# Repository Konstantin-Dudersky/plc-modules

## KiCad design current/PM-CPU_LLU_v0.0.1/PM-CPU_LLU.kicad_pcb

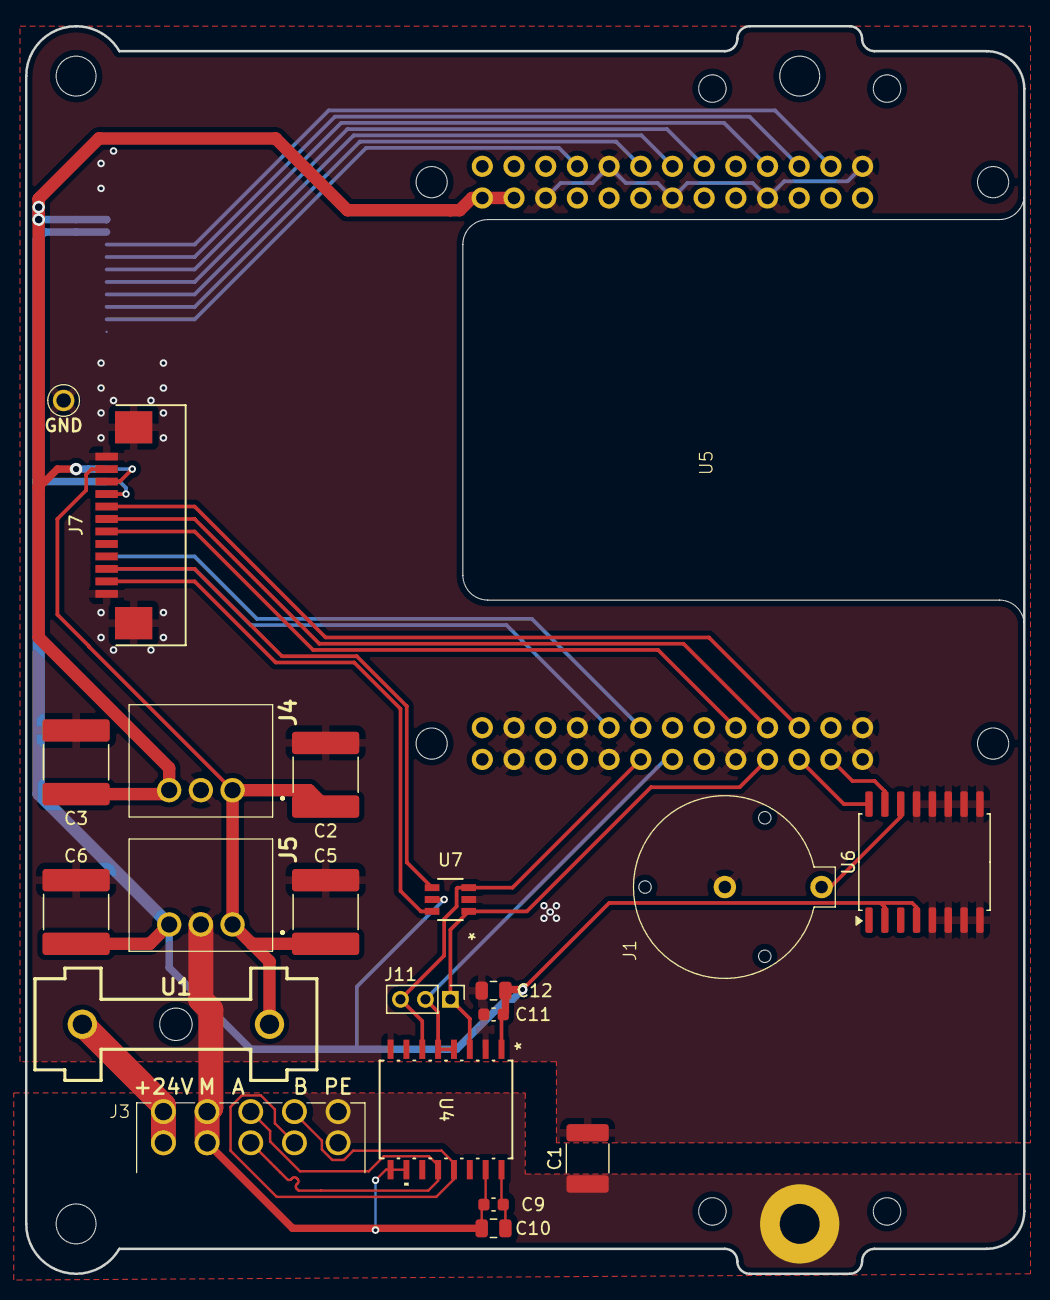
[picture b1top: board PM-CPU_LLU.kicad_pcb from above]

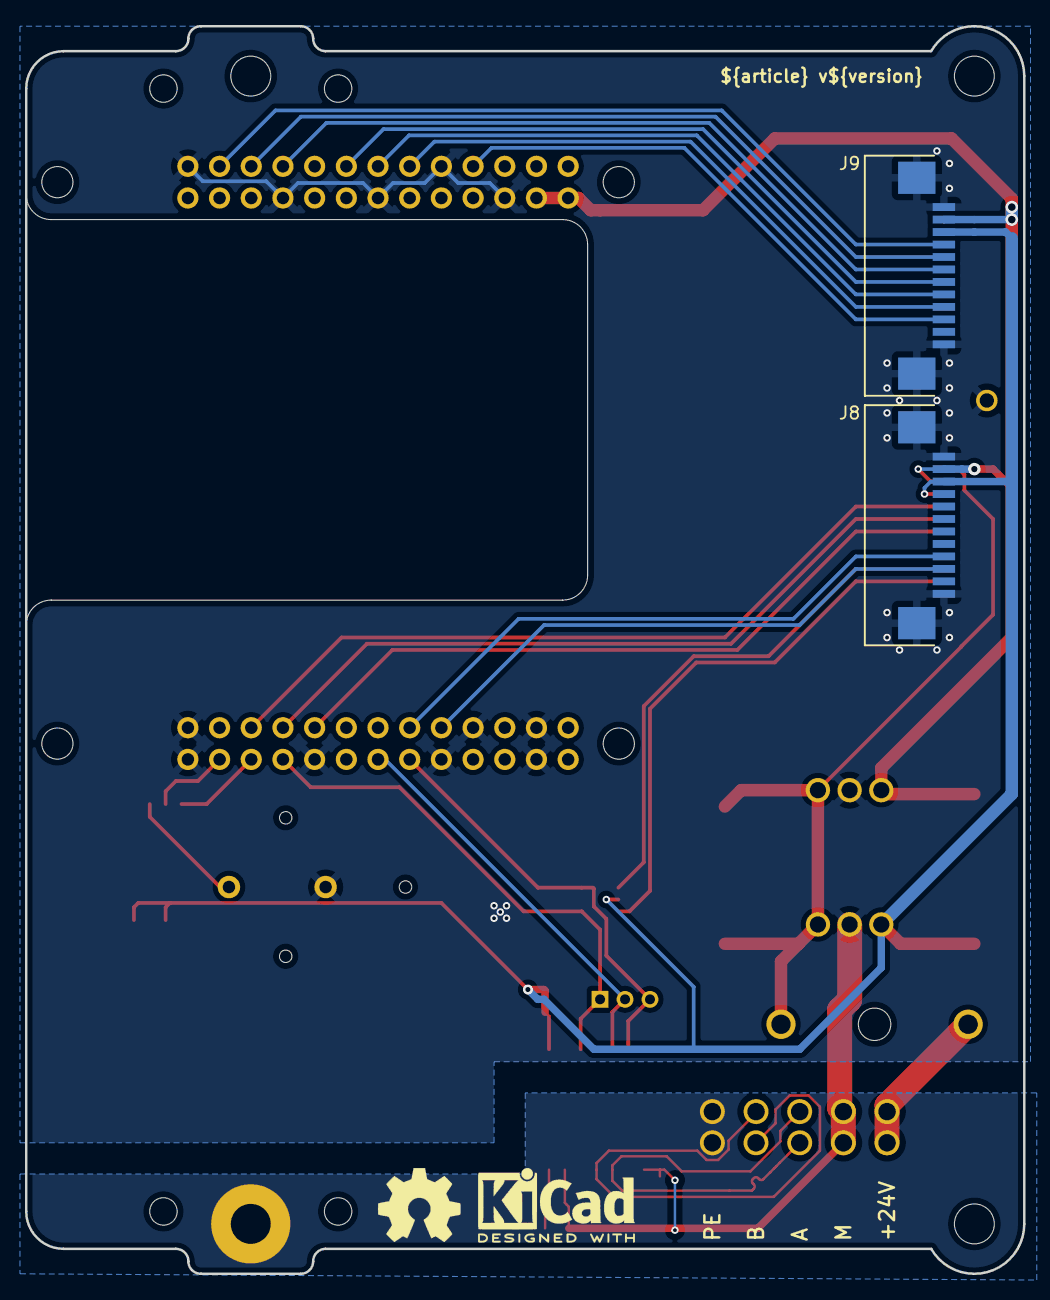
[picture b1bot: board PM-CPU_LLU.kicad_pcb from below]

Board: 2 copper layers, 80.0 x 100.0 mm, 30 parts (4 on the bottom side), 29 nets.

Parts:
C1: 4.7nF 2kV; C_1812_4532Metric
C2, C3, C5, C6: 22uF; C_2220_5750Metric
C9, C11: 100nF; C_0603_1608Metric
C10, C12: 10uF; C_0805_2012Metric
H1, H2, H3: MountingHole_M3
J1: BS-12-A1AJ002-F
J3: 15EDGRHC-THR-3.5-10P
J4: K7805-2000R3
J5: K7803-2000R3; K7805-2000R3
J7, J8, J9: AFA07-S10FCC-00; CONN10_AFA07-S12_JUS
J11: PinHeader_01x03_P2.00_THT_straight; PinHeader_1x03_P2.00mm_Vertical
PE1: PE
SP1: PM_LED-xx-v0.0.1
U1: 64900001039; 649-Series-Holder
U2: 5117
U4: CA-IS3098W; SOIC16-WBW_CLG
U5: LuckfoxLyraUltra
U6: DS3231; SOIC-16W_7.5x10.3mm_P1.27mm
U7: SN74LVC2G14DBVR; DBV6-M
kicad_logo: KiCad-Logo2_5mm_SilkScreen
oshw_logo: OSHW-Symbol_6.7x6mm_SilkScreen

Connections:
+3.3V_BUS: C9.1, C10.1, U4.16 (VISO)
+3.3V_CPU: C6.1, C11.1, C12.1, J5.3 (+VO), J7.9, J8.3, J9.3, U4.1 (VDD), U6.2 (VCC), U6.4 (~RST), U7.5 (VCC)
+5V_CPU: C3.1, J4.3 (+VO), J7.10, J8.2, J9.2, U5.10 (VSYS), U5.11 (VSYS)
+24V_BUS: J3.1, J3.6 (Pin_2), U1.1
+24V_fuse: C2.1, C5.1, J4.1 (VIN), J5.1 (VIN), J7.11, U1.2
/A: J3.3, J3.8 (Pin_6), U4.12 (A)
/B: J3.4, J3.9 (Pin_8), U4.13 (B)
/I2C0_SCL: J8.10, U5.24 (RM_IO24)
/I2C0_SDA: J8.9, U5.25 (RM_IO25)
/I2C1_SCL: U5.3A (RM_IO18), U6.16 (SCL)
/I2C1_SDA: U5.3B (RM_IO20), U6.15 (SDA)
/LED_0: J7.8, U5.2A (RM_IO30)
/LED_1: J7.7, U5.29 (RM_IO29)
/LED_2: J7.6, U5.28 (RM_IO28)
/SPI_CS0: J9.7, U5.07 (RM_IO5)
/SPI_CS1: J9.8, U5.06 (RM_IO4)
/SPI_CS2: J9.9, U5.05 (RM_IO3)
/SPI_CS3: J9.10, U5.03 (RM_IO2)
/SPI_MISO: J9.5, U5.0A (RM_IO7)
/SPI_MOSI: J9.4, U5.0B (RM_IO8)
/SPI_SCK: J9.6, U5.09 (RM_IO6)
/UART_RTS: J11.2, U4.4 (RE), U4.5 (DE), U5.36
/UART_RX: J11.1, U4.3 (RO), U5.39 (RM_IO17), U7.1 (1A)
/UART_RX_LED: J7.2, U7.6 (1Y)
/UART_TX: J11.3, U4.6 (DI), U5.35 (RM_IO16), U7.3 (2A)
/UART_TX_LED: J7.3, U7.4 (2Y)
/Vbat: J1.1, U6.14 (VBAT)
GND_BUS: C1.2, C2.2, C3.2, C5.2, C6.2, C9.2, C10.2, C11.2, C12.2, J1.2, J3.2 (Pin_3), J3.7 (Pin_4), J4.2 (GND), J5.2 (GND), J7.1, J7.12 (Pin_11), J7.13 (Pin_11), J8.1, J8.12 (Pin_11), J8.13 (Pin_11), J9.1, J9.12 (Pin_11), J9.13 (Pin_11), U2.1, U4.2 (GNDA), U4.8 (GNDA), U4.9 (GNDB), U4.10 (SEL), U4.15 (GNDB), U5.0C (GND), U5.2C (GND), U5.3C (GND), U5.04 (GND), U5.12 (GND), U5.16 (GND), U5.19 (GND), U5.21 (GND), U5.23 (GND), U5.31 (GND), U5.34 (GND), U5.38 (GND), U6.5 (GND), U6.6 (GND), U6.7 (GND), U6.8 (GND), U6.9 (GND), U6.10 (GND), U6.11 (GND), U6.12 (GND), U6.13 (GND), U7.2 (GND)
PE: C1.1, J3.5 (Pin_9), J3.10, PE1.1

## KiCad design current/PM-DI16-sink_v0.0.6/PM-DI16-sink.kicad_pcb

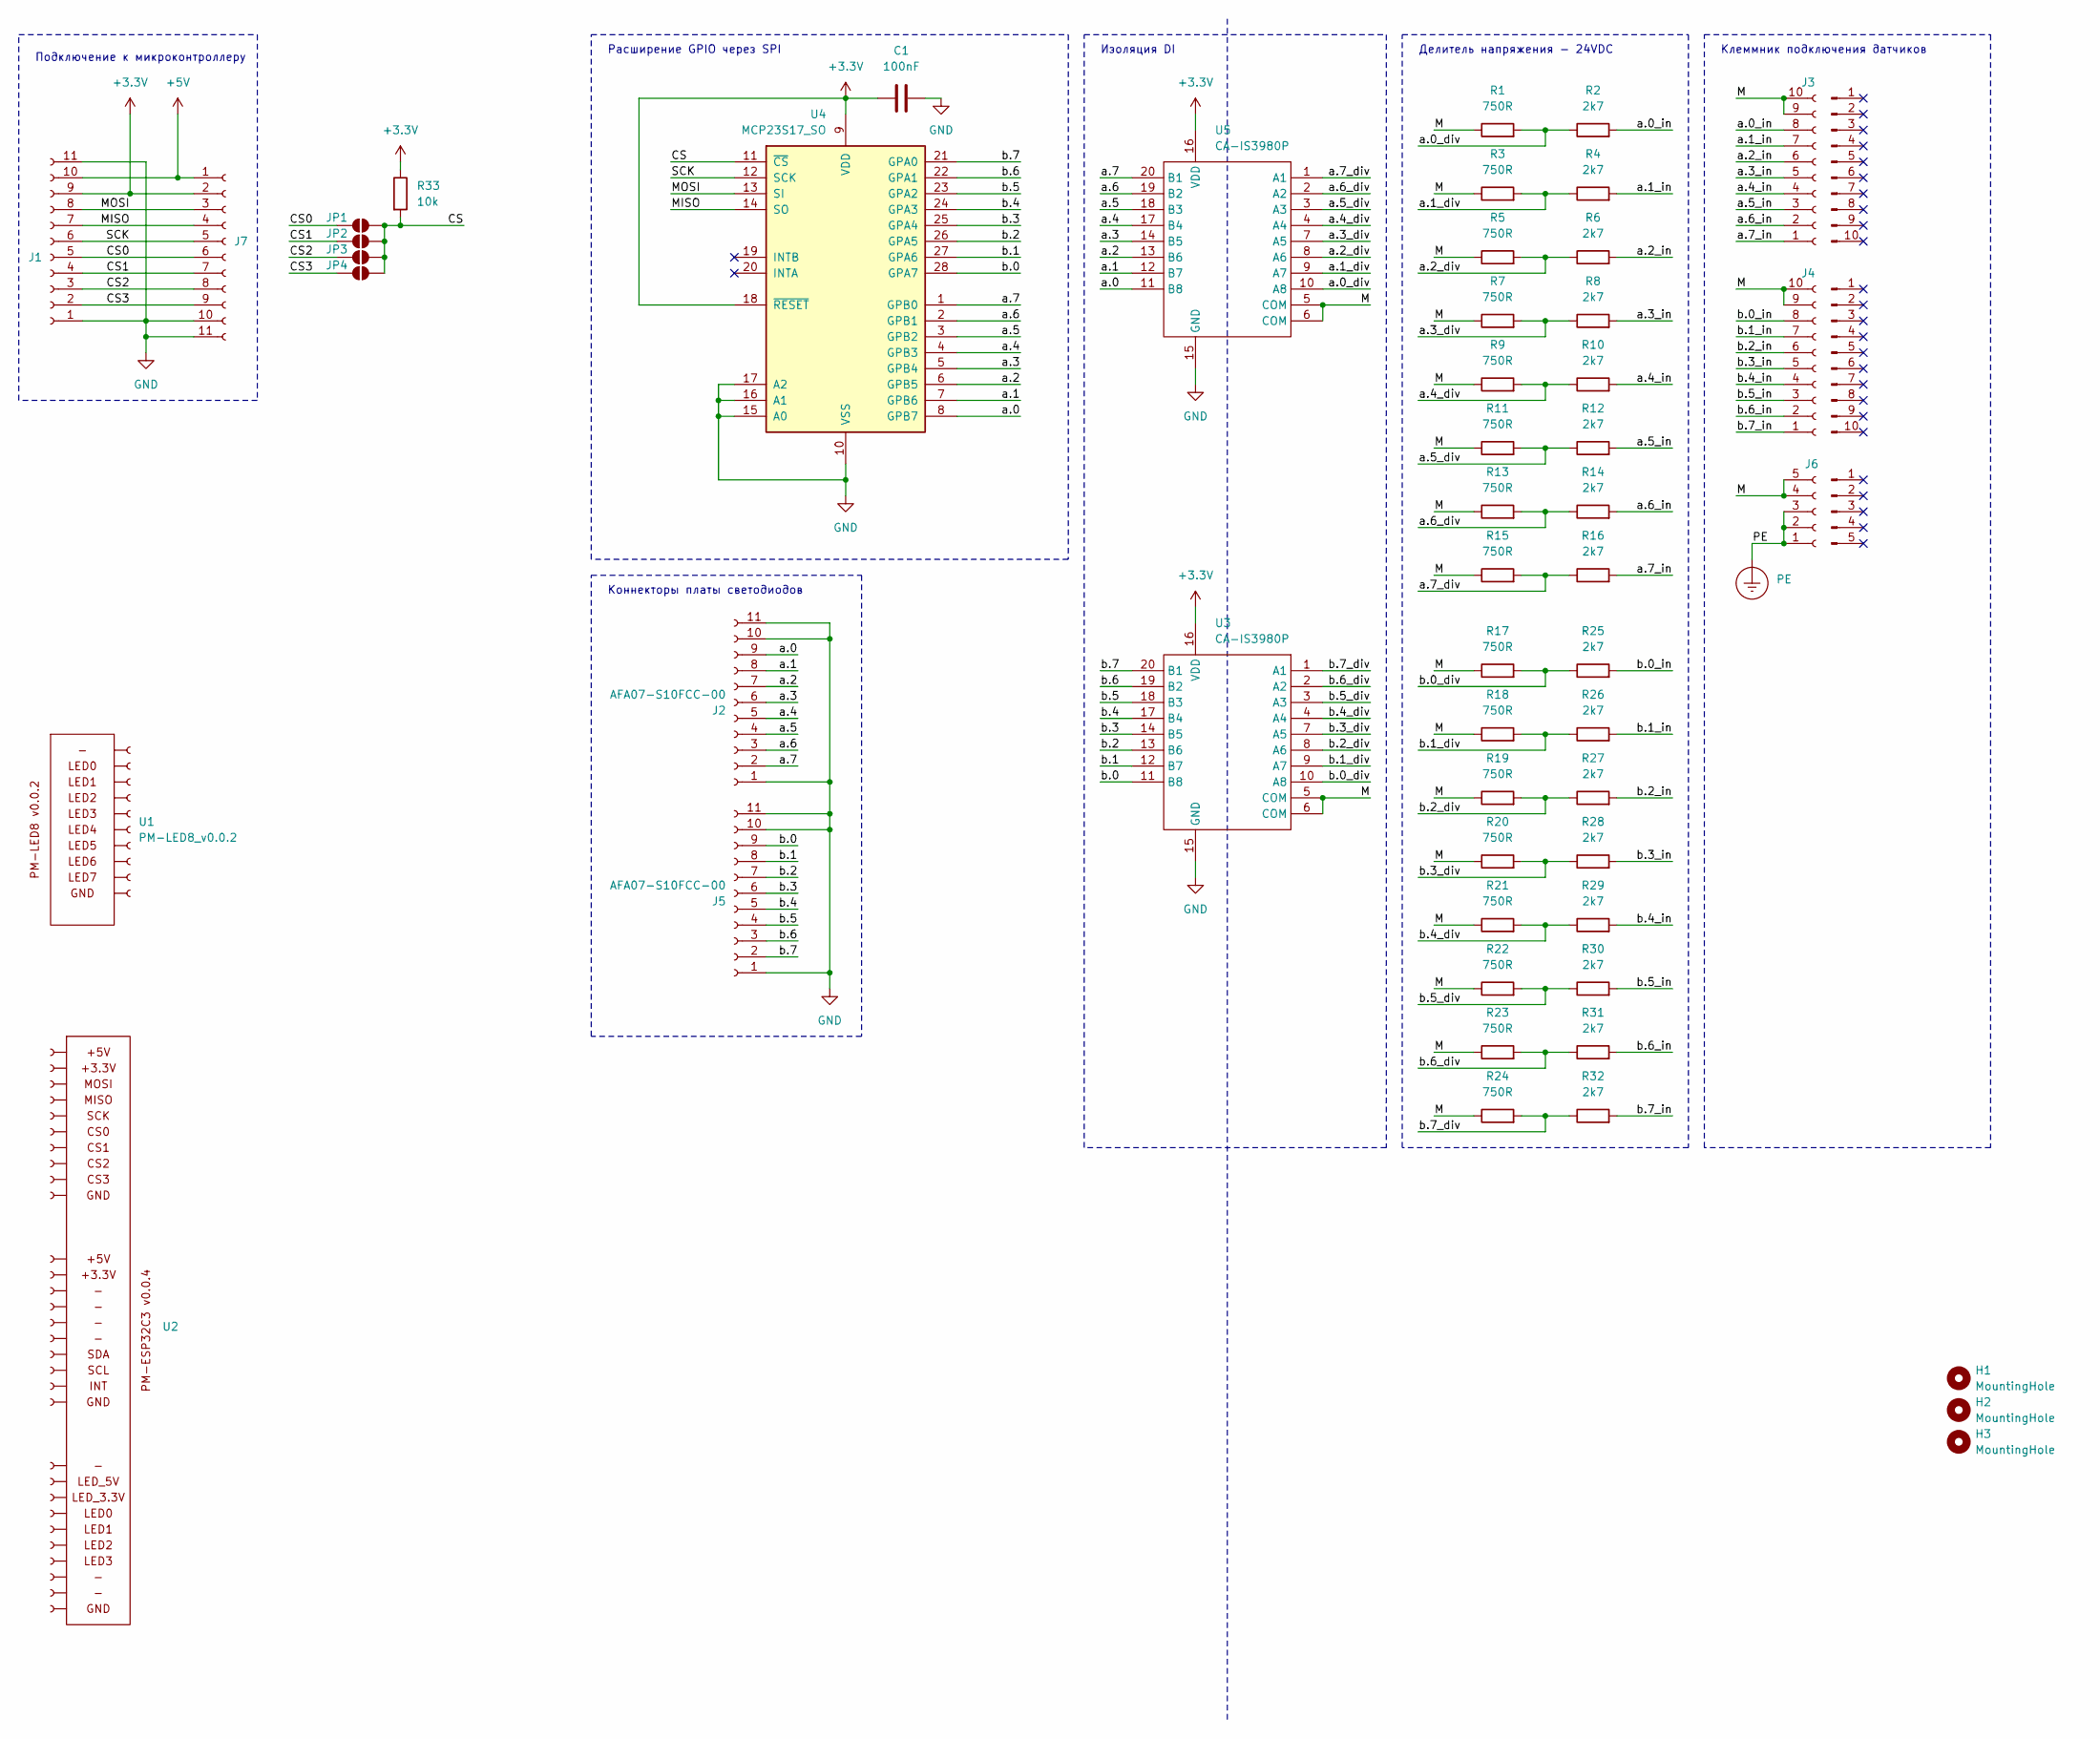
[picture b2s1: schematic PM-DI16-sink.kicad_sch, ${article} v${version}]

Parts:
C1: 100nF; C_0603_1608Metric; part_ipn C_100nF_16V_0603_MLCC-X7R
H1, H2, H3: MountingHole; MountingHole_3.2mm_M3
J1, J2, J5, J7: AFA07-S10FCC-00; CONN10_AFA07-S10_JUS; part_ipn AFA07-S10FCC-00
J3, J4: 15EDGRC-3.5-10P; part_ipn 15EDGRC-3.5-10P
J6: 15EDGRC-3.5-05P; part_ipn 15EDGRC-3.5-05P
J8, J9: 15EDGK-3.5-10P; part_ipn 15EDGK-3.5-10P
J10: 15EDGK-3.5-05P; part_ipn 15EDGK-3.5-05P
JP1, JP2, JP3, JP4: SolderJumper_2_Open; SolderJumper-2_P1.3mm_Open_RoundedPad1.0x1.5mm
PE1: PE
R1, R3, R5, R7, R9, R11, R13, R15, R17, R18, R19, R20, R21, R22, R23, R24: 750R; R_0603_1608Metric; part_ipn R_750R_0603_1%
R2, R4, R6, R8, R10, R12, R14, R16, R25, R26, R27, R28, R29, R30, R31, R32: 2k7; R_0603_1608Metric; part_ipn R_2k7_0603_1%
R33: 10k; R_0603_1608Metric; part_ipn R_10k_0603_1%
U1: PM-LED8_v0.0.2; PM-LED_v0.0.2; part_ipn PM-LED8_v0.0.2
U2: PM-ESP32C3_v0.0.4; part_ipn PM-ESP32C3_v0.0.4
U3, U5: CA-IS3980P; SSOP-20_3.9x8.7mm_P0.635mm; part_ipn CA-IS3980P
U4: MCP23S17_SO; SOIC-28W_7.5x17.9mm_P1.27mm; part_ipn MCP23S17-E/SO

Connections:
+3.3V: C1.1, J1.9, J7.2, R33.1, U3.16 (VDD), U4.9 (VDD), U4.18 (~RESET), U5.16 (VDD)
+5V: J1.10, J7.1
/CS: JP1.2 (B), JP2.2 (B), JP3.2 (B), JP4.2 (B), R33.2, U4.11 (~CS)
/CS0: J1.5, J7.6, JP1.1 (A)
/CS1: J1.4, J7.7, JP2.1 (A)
/CS2: J1.3, J7.8, JP3.1 (A)
/CS3: J1.2, J7.9, JP4.1 (A)
/M: J3.9, J3.10, J4.9, J4.10, J6.4, J6.5, R1.1, R3.1, R5.1, R7.1, R9.1, R11.1, R13.1, R15.1, R17.1, R18.1, R19.1, R20.1, R21.1, R22.1, R23.1, R24.1, U3.5 (COM), U3.6 (COM), U5.5 (COM), U5.6 (COM)
/MISO: J1.7, J7.4, U4.14 (SO)
/MOSI: J1.8, J7.3, U4.13 (SI)
/PE: J6.1, J6.2, J6.3, PE1.1
/SCK: J1.6, J7.5, U4.12 (SCK)
/a.0: J2.9, U4.8 (GPB7), U5.11 (B8)
/a.0_div: R1.2, R2.1, U5.10 (A8)
/a.0_in: J3.8, R2.2
/a.1: J2.8, U4.7 (GPB6), U5.12 (B7)
/a.1_div: R3.2, R4.1, U5.9 (A7)
/a.1_in: J3.7, R4.2
/a.2: J2.7, U4.6 (GPB5), U5.13 (B6)
/a.2_div: R5.2, R6.1, U5.8 (A6)
/a.2_in: J3.6, R6.2
/a.3: J2.6, U4.5 (GPB4), U5.14 (B5)
/a.3_div: R7.2, R8.1, U5.7 (A5)
/a.3_in: J3.5, R8.2
/a.4: J2.5, U4.4 (GPB3), U5.17 (B4)
/a.4_div: R9.2, R10.1, U5.4 (A4)
/a.4_in: J3.4, R10.2
/a.5: J2.4, U4.3 (GPB2), U5.18 (B3)
/a.5_div: R11.2, R12.1, U5.3 (A3)
/a.5_in: J3.3, R12.2
/a.6: J2.3, U4.2 (GPB1), U5.19 (B2)
/a.6_div: R13.2, R14.1, U5.2 (A2)
/a.6_in: J3.2, R14.2
/a.7: J2.2, U4.1 (GPB0), U5.20 (B1)
/a.7_div: R15.2, R16.1, U5.1 (A1)
/a.7_in: J3.1, R16.2
/b.0: J5.9, U3.11 (B8), U4.28 (GPA7)
/b.0_div: R17.2, R25.1, U3.10 (A8)
/b.0_in: J4.8, R25.2
/b.1: J5.8, U3.12 (B7), U4.27 (GPA6)
/b.1_div: R18.2, R26.1, U3.9 (A7)
/b.1_in: J4.7, R26.2
/b.2: J5.7, U3.13 (B6), U4.26 (GPA5)
/b.2_div: R19.2, R27.1, U3.8 (A6)
/b.2_in: J4.6, R27.2
/b.3: J5.6, U3.14 (B5), U4.25 (GPA4)
/b.3_div: R20.2, R28.1, U3.7 (A5)
/b.3_in: J4.5, R28.2
/b.4: J5.5, U3.17 (B4), U4.24 (GPA3)
/b.4_div: R21.2, R29.1, U3.4 (A4)
/b.4_in: J4.4, R29.2
/b.5: J5.4, U3.18 (B3), U4.23 (GPA2)
/b.5_div: R22.2, R30.1, U3.3 (A3)
/b.5_in: J4.3, R30.2
/b.6: J5.3, U3.19 (B2), U4.22 (GPA1)
/b.6_div: R23.2, R31.1, U3.2 (A2)
/b.6_in: J4.2, R31.2
/b.7: J5.2, U3.20 (B1), U4.21 (GPA0)
/b.7_div: R24.2, R32.1, U3.1 (A1)
/b.7_in: J4.1, R32.2
GND: C1.2, J1.1, J1.11, J2.1, J2.10, J2.11, J5.1, J5.10, J5.11, J7.10, J7.11, U3.15 (GND), U4.10 (VSS), U4.15 (A0), U4.16 (A1), U4.17 (A2), U5.15 (GND)

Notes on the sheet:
Делитель напряжения - 24VDC
Подключение к микроконтроллеру
Клеммник подключения датчиков
Расширение GPIO через SPI
Изоляция DI
Коннекторы платы светодиодов

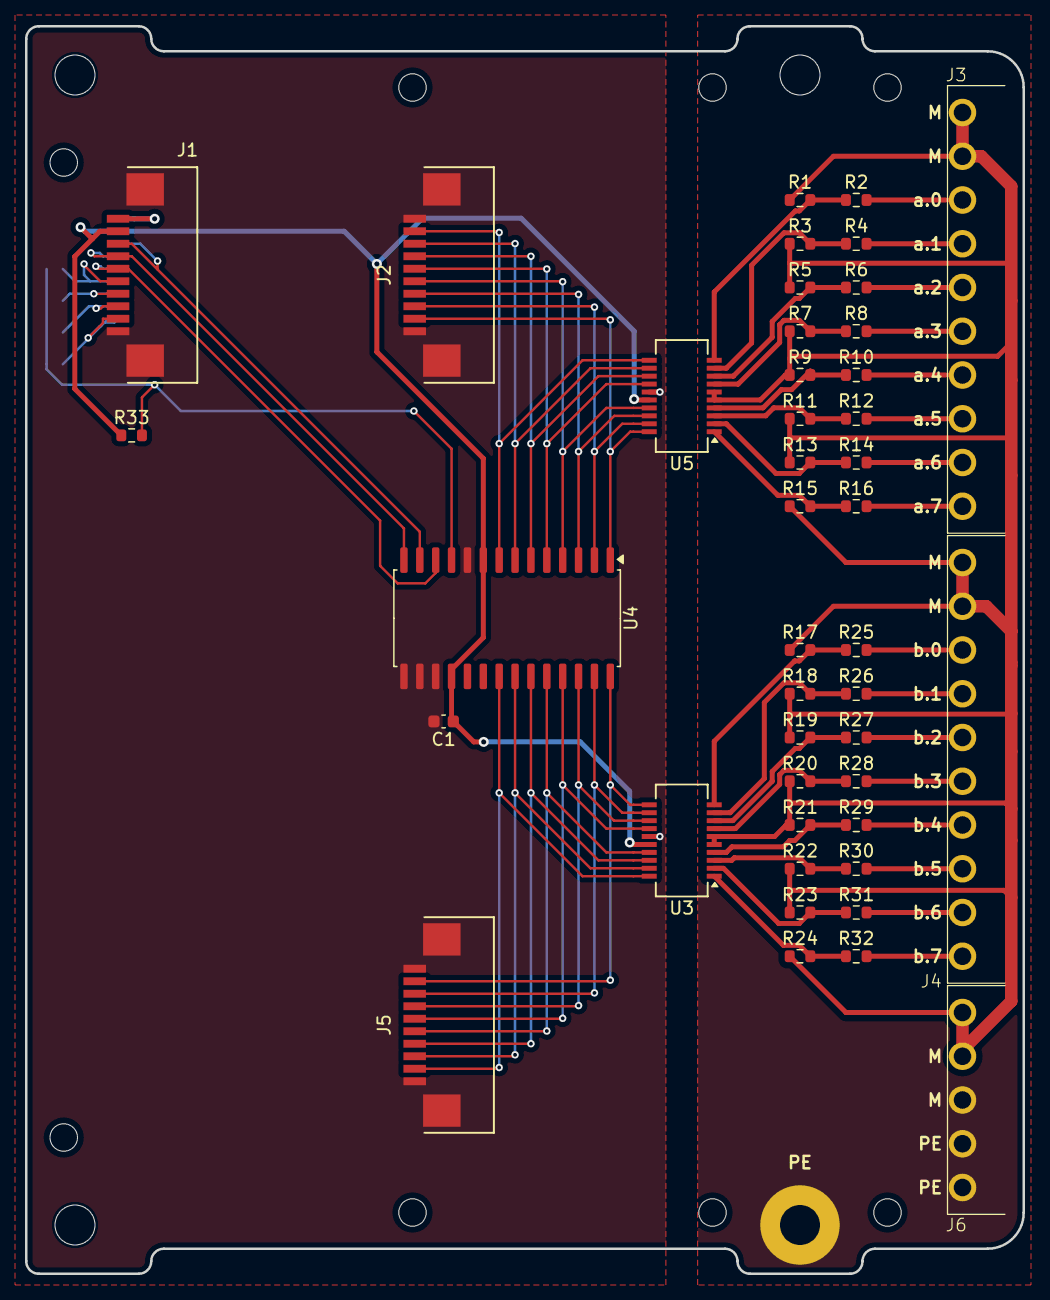
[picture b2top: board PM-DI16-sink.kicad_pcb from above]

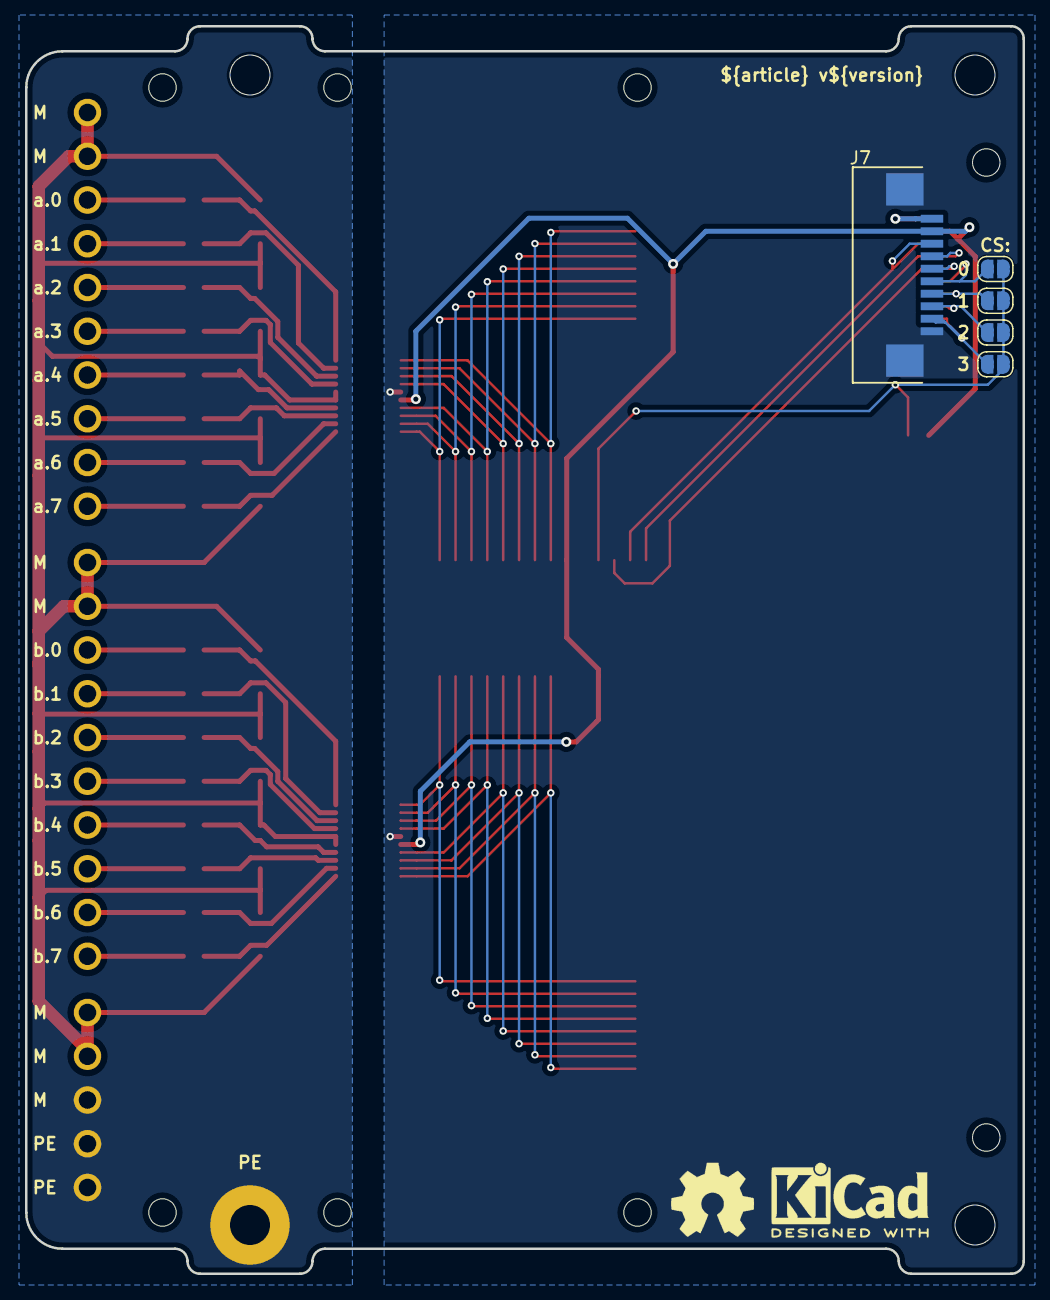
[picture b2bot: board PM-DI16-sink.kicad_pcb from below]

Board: 2 copper layers, 79.8 x 99.8 mm, 56 parts (7 on the bottom side), 61 nets.

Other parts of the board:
kicad_logo: KiCad-Logo2_5mm_SilkScreen
oshw_logo: OSHW-Symbol_6.7x6mm_SilkScreen

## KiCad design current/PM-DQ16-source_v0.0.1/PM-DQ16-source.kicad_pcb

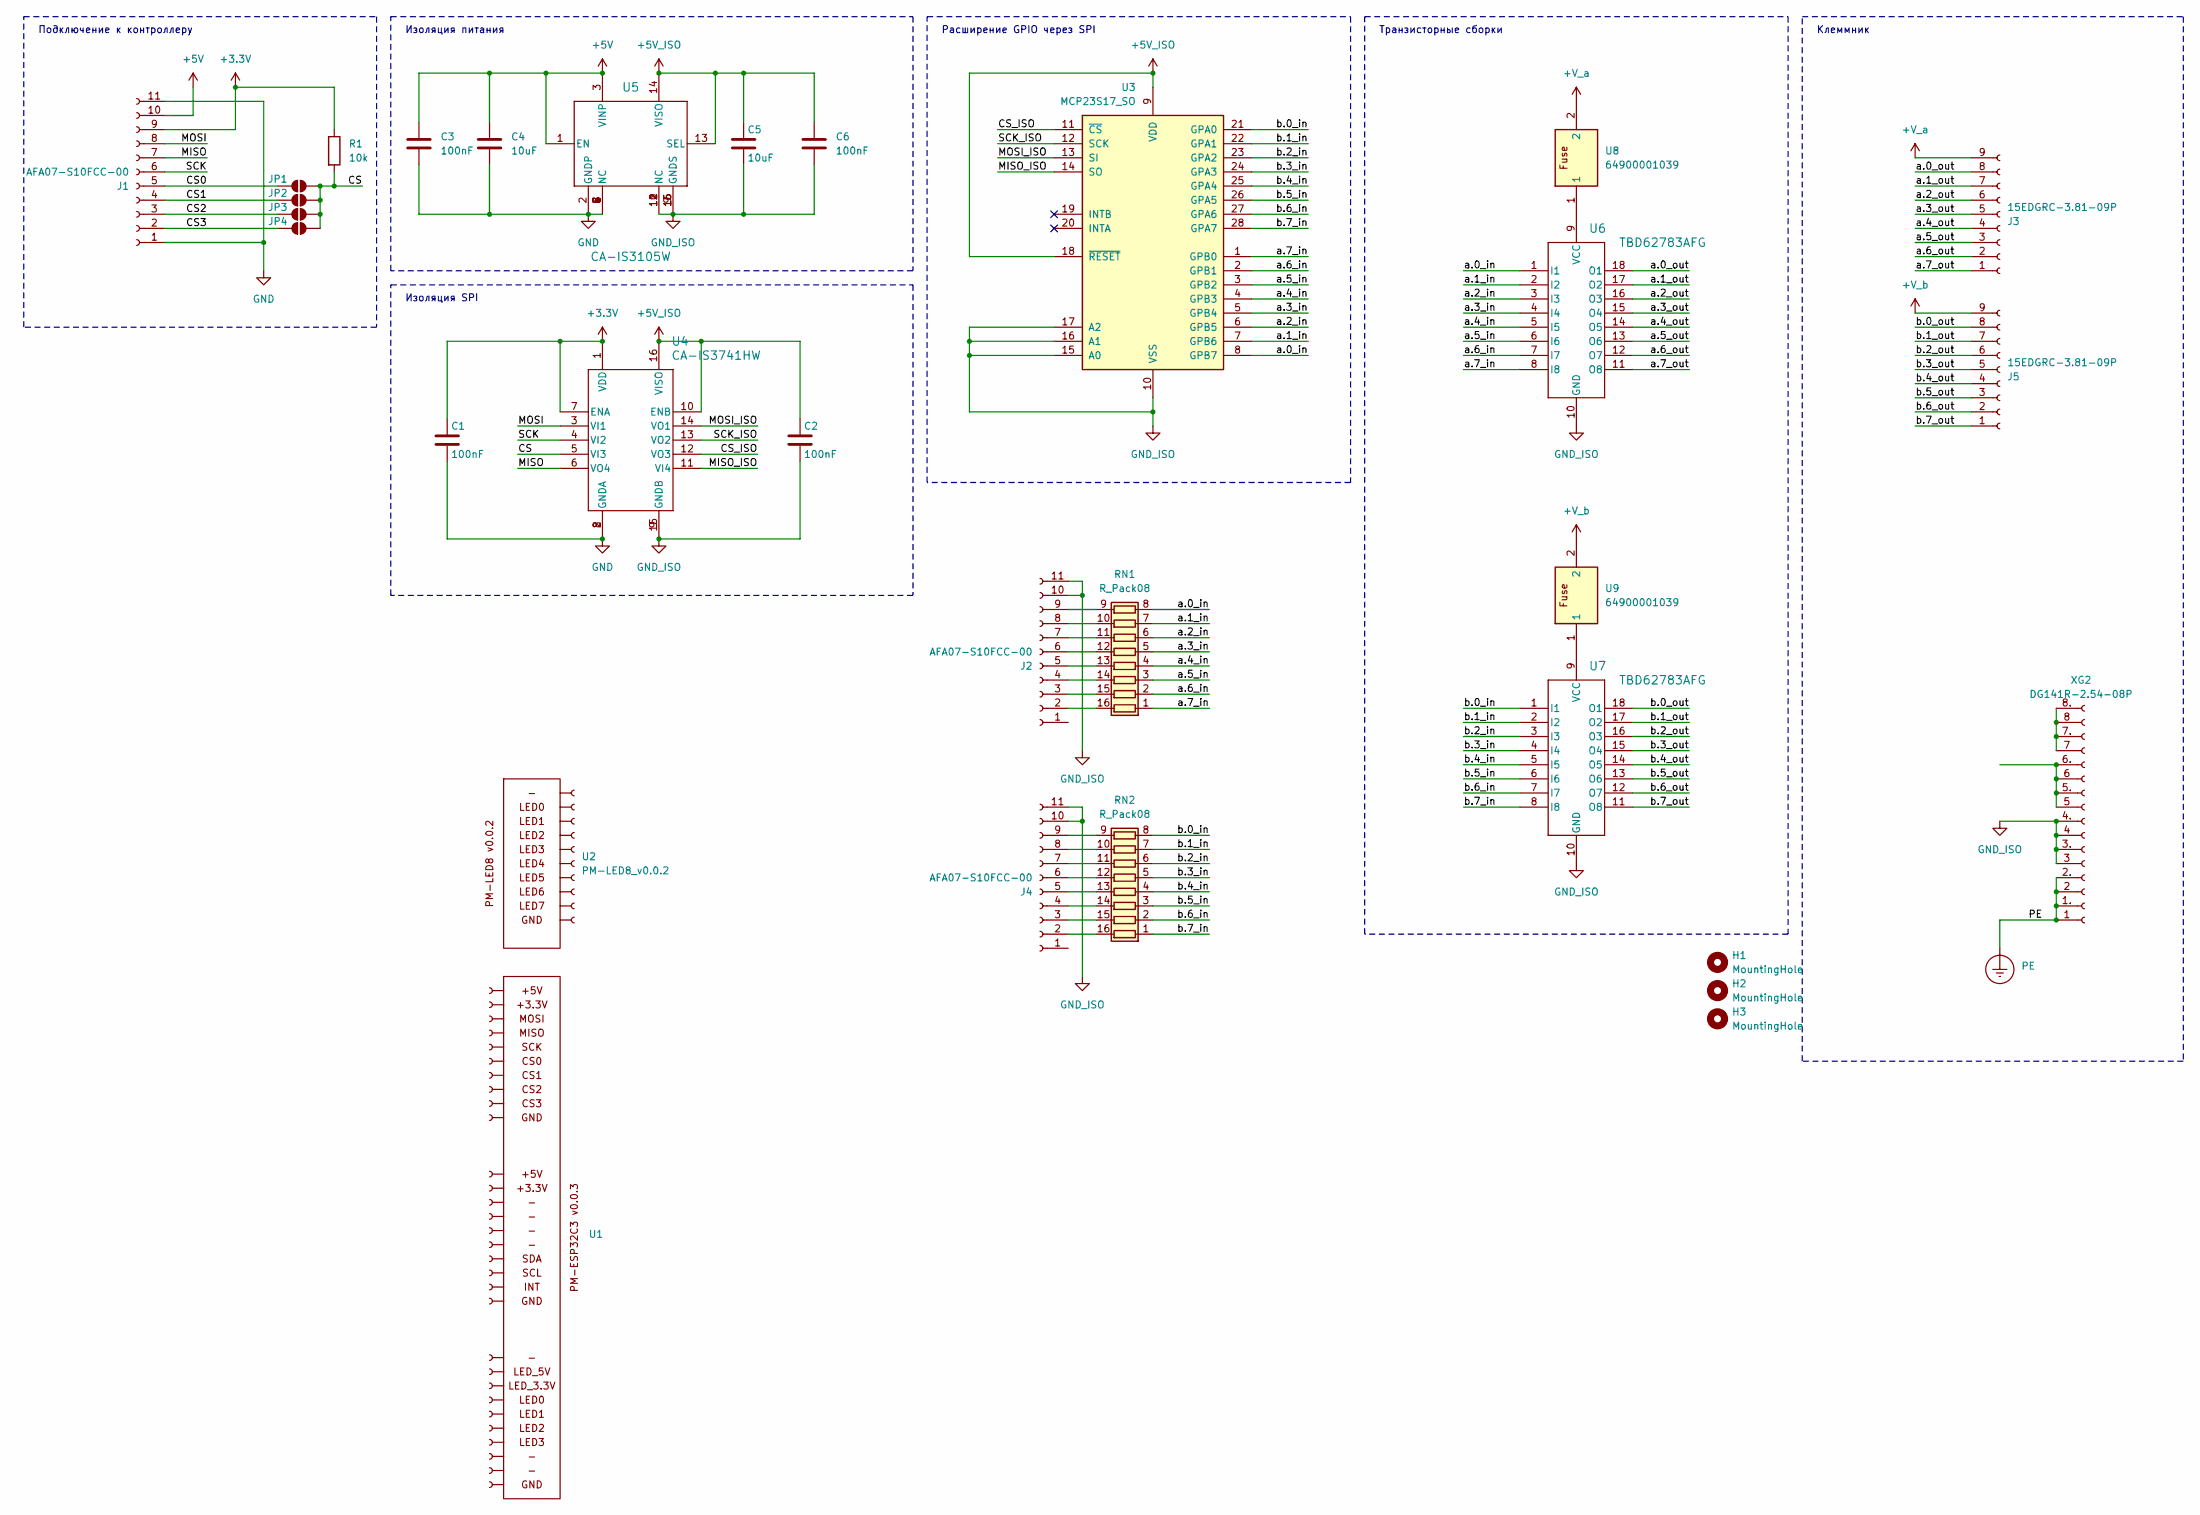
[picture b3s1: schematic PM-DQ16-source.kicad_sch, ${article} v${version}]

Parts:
C1, C2, C3, C6: 100nF; C_0603_1608Metric; part_ipn C_100nF_16V_0603_MLCC-X7R
C4, C5: 10uF; C_0603_1608Metric; part_ipn C_10uF_16V_0603_MLCC-X5R
H1, H2, H3: MountingHole; MountingHole_3.2mm_M3
J1, J2, J4: AFA07-S10FCC-00; CONN10_AFA07-S10_JUS; part_ipn AFA07-S10FCC-00
J3, J5: 15EDGRC-3.81-09P; part_ipn 15EDGRC-3.81-09P
JP1, JP2, JP3, JP4: SolderJumper_2_Open; SolderJumper-2_P1.3mm_Open_RoundedPad1.0x1.5mm
PE1: PE
R1: 10k; R_0603_1608Metric; part_ipn R_10k_0603_1%
RN1, RN2: R_Pack08; R_Array_Convex_8x0602
U1: PM-ESP32C3_v0.0.3; part_ipn PM-ESP32C3_v0.0.3
U2: PM-LED8_v0.0.2; PM-LED_v0.0.2; part_ipn PM-LED8_v0.0.1
U3: MCP23S17_SO; SOIC-28W_7.5x17.9mm_P1.27mm; part_ipn MCP23S17-E/SO
U4: CA-IS3741HW; SOIC16-WBW_CLG-M; part_ipn CA-IS3741HW
U5: CA-IS3105W; SOIC16-WBW_CLG-M; part_ipn CA-IS3105W
U6, U7: TBD62783AFG; SOP18-P-375-1p27_TOS-M
U8, U9: 64900001039; Fuseholder; Manufacturer_Part_Number 64900001039; Mouser Part Number 576-64900001039
XG2: DG141R-2.54-08P; part_ipn DG141R-2.54-08P

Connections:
+3.3V: C1.1, J1.9, R1.1, U4.1 (VDD), U4.7 (ENA)
+5V: C3.1, C4.1, J1.10, U5.1 (EN), U5.3 (VINP)
+5V_ISO: C2.1, C5.1, C6.1, U3.9 (VDD), U3.18 (~RESET), U4.10 (ENB), U4.16 (VISO), U5.13 (SEL), U5.14 (VISO)
+V_a: J3.9, U8.2
+V_b: J5.9, U9.2
/CS: JP1.2 (B), JP2.2 (B), JP3.2 (B), JP4.2 (B), R1.2, U4.5 (VI3)
/CS0: J1.5, JP1.1 (A)
/CS1: J1.4, JP2.1 (A)
/CS2: J1.3, JP3.1 (A)
/CS3: J1.2, JP4.1 (A)
/CS_ISO: U3.11 (~CS), U4.12 (VO3)
/MISO: J1.7, U4.6 (VO4)
/MISO_ISO: U3.14 (SO), U4.11 (VI4)
/MOSI: J1.8, U4.3 (VI1)
/MOSI_ISO: U3.13 (SI), U4.14 (VO1)
/PE: PE1.1, XG2.1, XG2.1. (Pin_1), XG2.2, XG2.2. (Pin_1)
/SCK: J1.6, U4.4 (VI2)
/SCK_ISO: U3.12 (SCK), U4.13 (VO2)
/a.0_in: RN1.8 (R8.1), U3.8 (GPB7), U6.1 (I1)
/a.0_out: J3.8, U6.18 (O1)
/a.1_in: RN1.7 (R7.1), U3.7 (GPB6), U6.2 (I2)
/a.1_out: J3.7, U6.17 (O2)
/a.2_in: RN1.6 (R6.1), U3.6 (GPB5), U6.3 (I3)
/a.2_out: J3.6, U6.16 (O3)
/a.3_in: RN1.5 (R5.1), U3.5 (GPB4), U6.4 (I4)
/a.3_out: J3.5, U6.15 (O4)
/a.4_in: RN1.4 (R4.1), U3.4 (GPB3), U6.5 (I5)
/a.4_out: J3.4, U6.14 (O5)
/a.5_in: RN1.3 (R3.1), U3.3 (GPB2), U6.6 (I6)
/a.5_out: J3.3, U6.13 (O6)
/a.6_in: RN1.2 (R2.1), U3.2 (GPB1), U6.7 (I7)
/a.6_out: J3.2, U6.12 (O7)
/a.7_in: RN1.1 (R1.1), U3.1 (GPB0), U6.8 (I8)
/a.7_out: J3.1, U6.11 (O8)
/b.0_in: RN2.8 (R8.1), U3.21 (GPA0), U7.1 (I1)
/b.0_out: J5.8, U7.18 (O1)
/b.1_in: RN2.7 (R7.1), U3.22 (GPA1), U7.2 (I2)
/b.1_out: J5.7, U7.17 (O2)
/b.2_in: RN2.6 (R6.1), U3.23 (GPA2), U7.3 (I3)
/b.2_out: J5.6, U7.16 (O3)
/b.3_in: RN2.5 (R5.1), U3.24 (GPA3), U7.4 (I4)
/b.3_out: J5.5, U7.15 (O4)
/b.4_in: RN2.4 (R4.1), U3.25 (GPA4), U7.5 (I5)
/b.4_out: J5.4, U7.14 (O5)
/b.5_in: RN2.3 (R3.1), U3.26 (GPA5), U7.6 (I6)
/b.5_out: J5.3, U7.13 (O6)
/b.6_in: RN2.2 (R2.1), U3.27 (GPA6), U7.7 (I7)
/b.6_out: J5.2, U7.12 (O7)
/b.7_in: RN2.1 (R1.1), U3.28 (GPA7), U7.8 (I8)
/b.7_out: J5.1, U7.11 (O8)
GND: C1.2, C3.2, C4.2, J1.1, J1.11, U4.2 (GNDA), U4.8 (GNDA), U5.2 (GNDP), U5.4 (NC), U5.5 (NC), U5.6 (NC), U5.7 (NC), U5.8 (NC)
GND_ISO: C2.2, C5.2, C6.2, J2.10, J2.11, J4.10, J4.11, U3.10 (VSS), U3.15 (A0), U3.16 (A1), U3.17 (A2), U4.9 (GNDB), U4.15 (GNDB), U5.9 (GNDS), U5.10 (NC), U5.11 (NC), U5.12 (NC), U5.15 (GNDS), U5.16 (GNDS), U6.10 (GND), U7.10 (GND), XG2.3, XG2.3. (Pin_1), XG2.4, XG2.4. (Pin_1)
unnamed: J2.2, RN1.16 (R1.2)
unnamed: J2.3, RN1.15 (R2.2)
unnamed: J2.4, RN1.14 (R3.2)
unnamed: J2.5, RN1.13 (R4.2)
unnamed: J2.6, RN1.12 (R5.2)
unnamed: J2.7, RN1.11 (R6.2)
unnamed: J2.8, RN1.10 (R7.2)
unnamed: J2.9, RN1.9 (R8.2)
unnamed: J4.2, RN2.16 (R1.2)
unnamed: J4.3, RN2.15 (R2.2)
unnamed: J4.4, RN2.14 (R3.2)
unnamed: J4.5, RN2.13 (R4.2)
unnamed: J4.6, RN2.12 (R5.2)
unnamed: J4.7, RN2.11 (R6.2)
unnamed: J4.8, RN2.10 (R7.2)
unnamed: J4.9, RN2.9 (R8.2)
unnamed: U6.9 (VCC), U8.1
unnamed: U7.9 (VCC), U9.1
unnamed: XG2.5, XG2.5. (Pin_1), XG2.6, XG2.6. (Pin_1)
unnamed: XG2.7, XG2.7. (Pin_1), XG2.8, XG2.8. (Pin_1)

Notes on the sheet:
Изоляция SPI
Расширение GPIO через SPI
Подключение к контроллеру
Транзисторные сборки
Клеммник
Изоляция питания

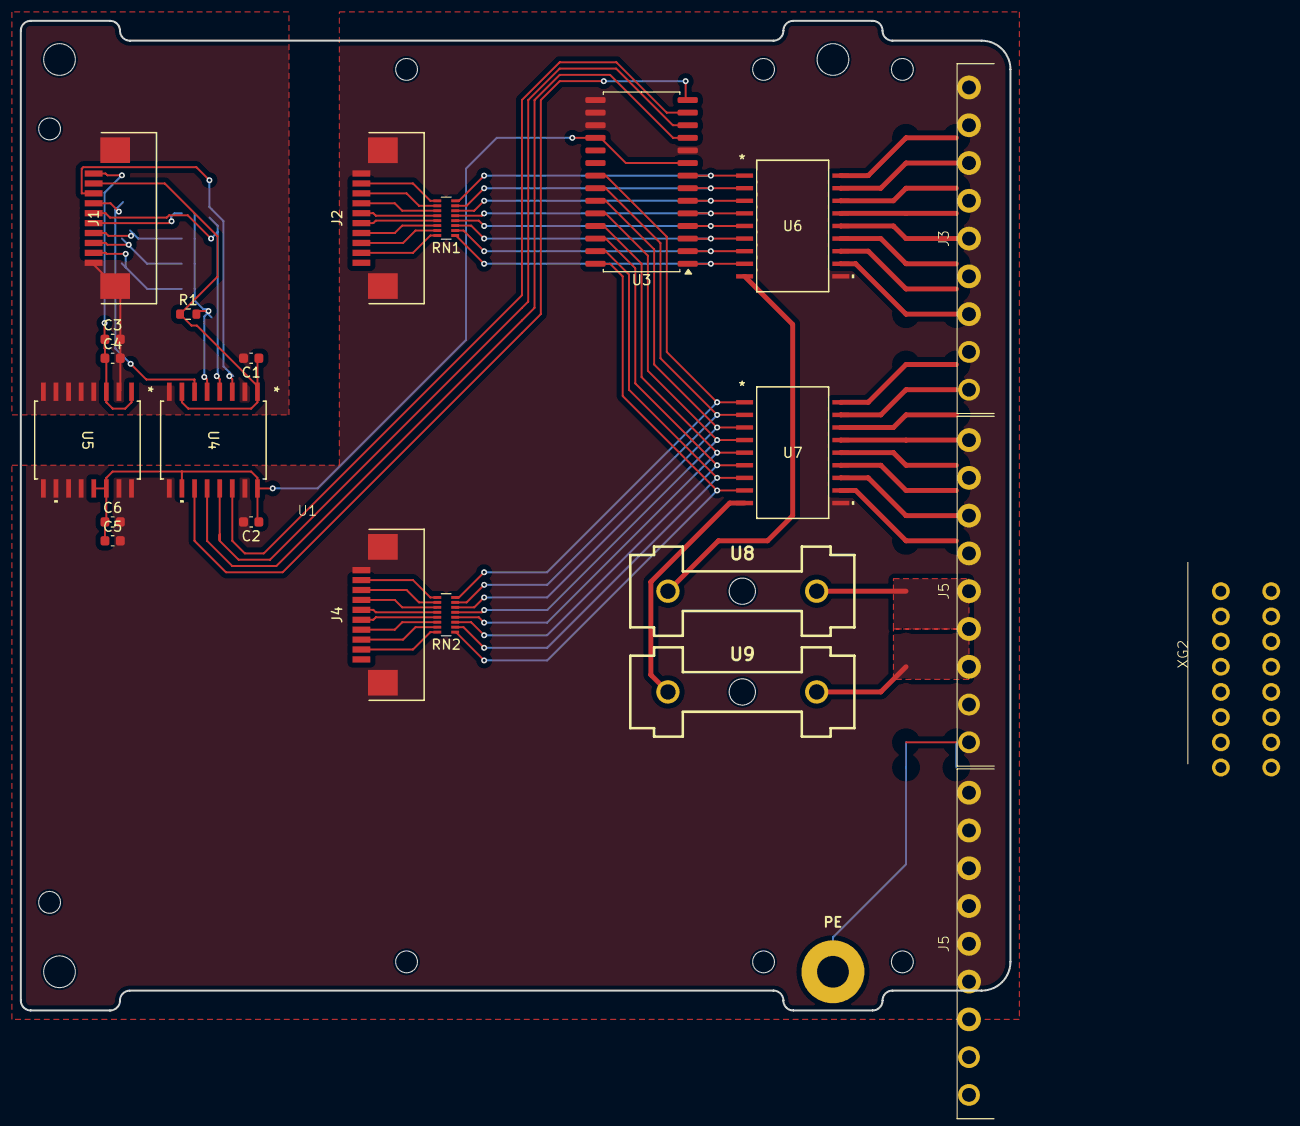
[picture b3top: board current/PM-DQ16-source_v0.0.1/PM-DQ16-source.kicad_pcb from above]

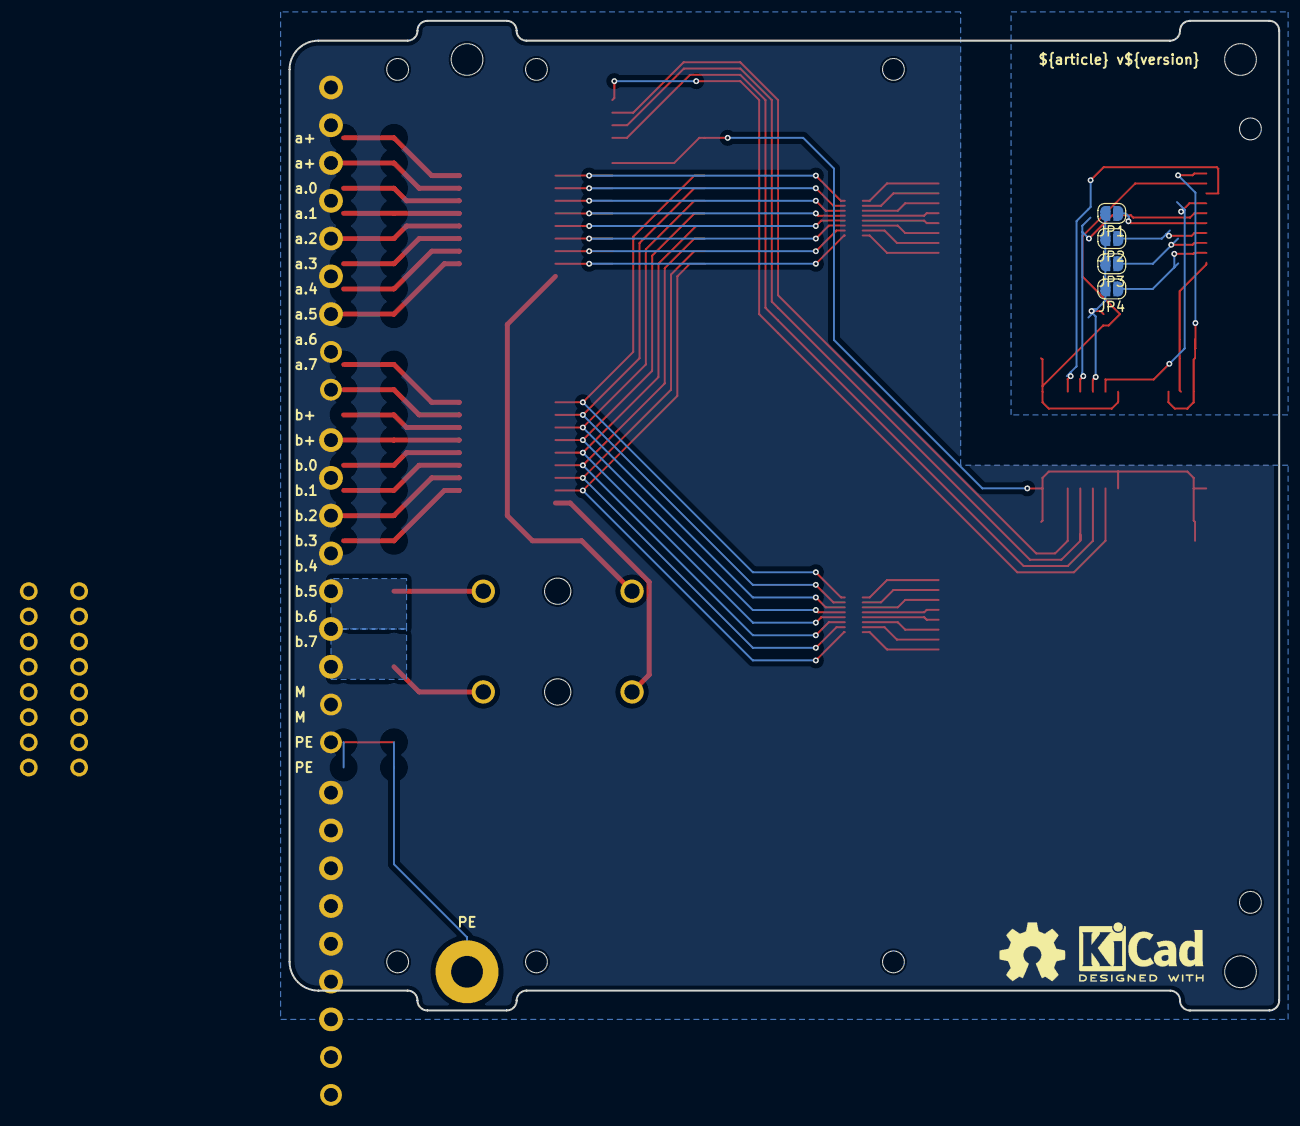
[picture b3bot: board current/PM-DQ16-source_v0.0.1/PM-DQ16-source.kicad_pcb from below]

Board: 2 copper layers, 99.8 x 99.8 mm, 35 parts (6 on the bottom side), 72 nets.

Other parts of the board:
J5#2: 15EDGRC-3.81-09P
kicad_logo: KiCad-Logo2_5mm_SilkScreen
oshw_logo: OSHW-Symbol_6.7x6mm_SilkScreen
